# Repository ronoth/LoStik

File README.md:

# LoStik

LoStik is an affordable, easy to use, LoRaWAN™ compatible device. It lets IoT (Internet of Things) integrators, network testers, and hobbyists get connected to a LoRa® network faster, diagnose network issues more easily, and build new and exciting connected devices.  LoStik is currently available to purchase on [Crowd Supply](https://www.crowdsupply.com/third-venture/lostik) and [Connected Things Store](https://connectedthings.store/gb/search?controller=search&s=lostik).

## Examples

Python examples require Python 3.  Be sure to install the dependiencies in requirements.txt

    pip install -r requirements.txt

### Miniterm

miniterm.py is a light weight terminal emulator that works well with LoRa stick. 
The RN2903/R2483 radios require \r\n line ending and run at 57600 baud.

    ./miniterm.py --echo /dev/ttyUSB0 57600

### Blinky

blinky.py is for testing the user LEDs on the LoRa Stik.  There is a red led tied to GPIO11 and a blue led tied to GPIO10. 

    ./blinky.py  -m blue -d 1 /dev/ttyUSB0

will blink the blue led once per second

    ./blinky.py -m both -d .5 /dev/ttyUSB0

will alternate the blue and red leds every .5 seconds.

### Packet Radio

radio_receiver.py and radio_sender.py are used for sending LoRa packets between two LoRa Stiks without the need for a LoRaWAN gateway.  The included example sends a unix timestamp packet every 2 seconds and the receiver prints the incoming packets to stdout.

## Resources

For detailed infomation about available commands checkout one of the following docs:
* [RN2903 Command Reference](http://ww1.microchip.com/downloads/en/DeviceDoc/40001811A.pdf)
* [RN2843 Command Reference](http://ww1.microchip.com/downloads/en/DeviceDoc/40001784B.pdf)

### GUI
Microchip offers a programm called "Lora Dev Utility" that is part of the [LoRa Development Suite](https://www.microchip.com/developmenttools/ProductDetails/dv164140-1)

## Platform Notes

For platform specific notes see:

* [Windows](docs/windows.md)
* [Mac](docs/mac.md)
* [Linux](docs/linux.md)

## License

### Software

All software and example scripts are MIT licensed.  For details see [LICENSE](blob/master/LICENSE)

### Hardware
Hardware design and schematics are licenede under Creative Commons CC-BY-SA-NC  For details see [hardware/LICENSE.md](blob/master/hardware/LICENSE.md)

### User LEDS

LoStik has two user LEDs that you can control via the UART interface on GPIO10 and GPIO11 and can be accessed using the following commands:

```sys set pindig GPIO10 1``` (turns on blue LED)

```sys set pindig GPIO10 0``` (turns off blue LED)

```sys set pindig GPIO11 1``` (turns on red LED)

```sys set pindig GPIO11 0``` (turns off red LED)

<sup>LoRa® and LoRaWAN™ are trademarks of Semtech Corporation or its subsidiaries.</sup>

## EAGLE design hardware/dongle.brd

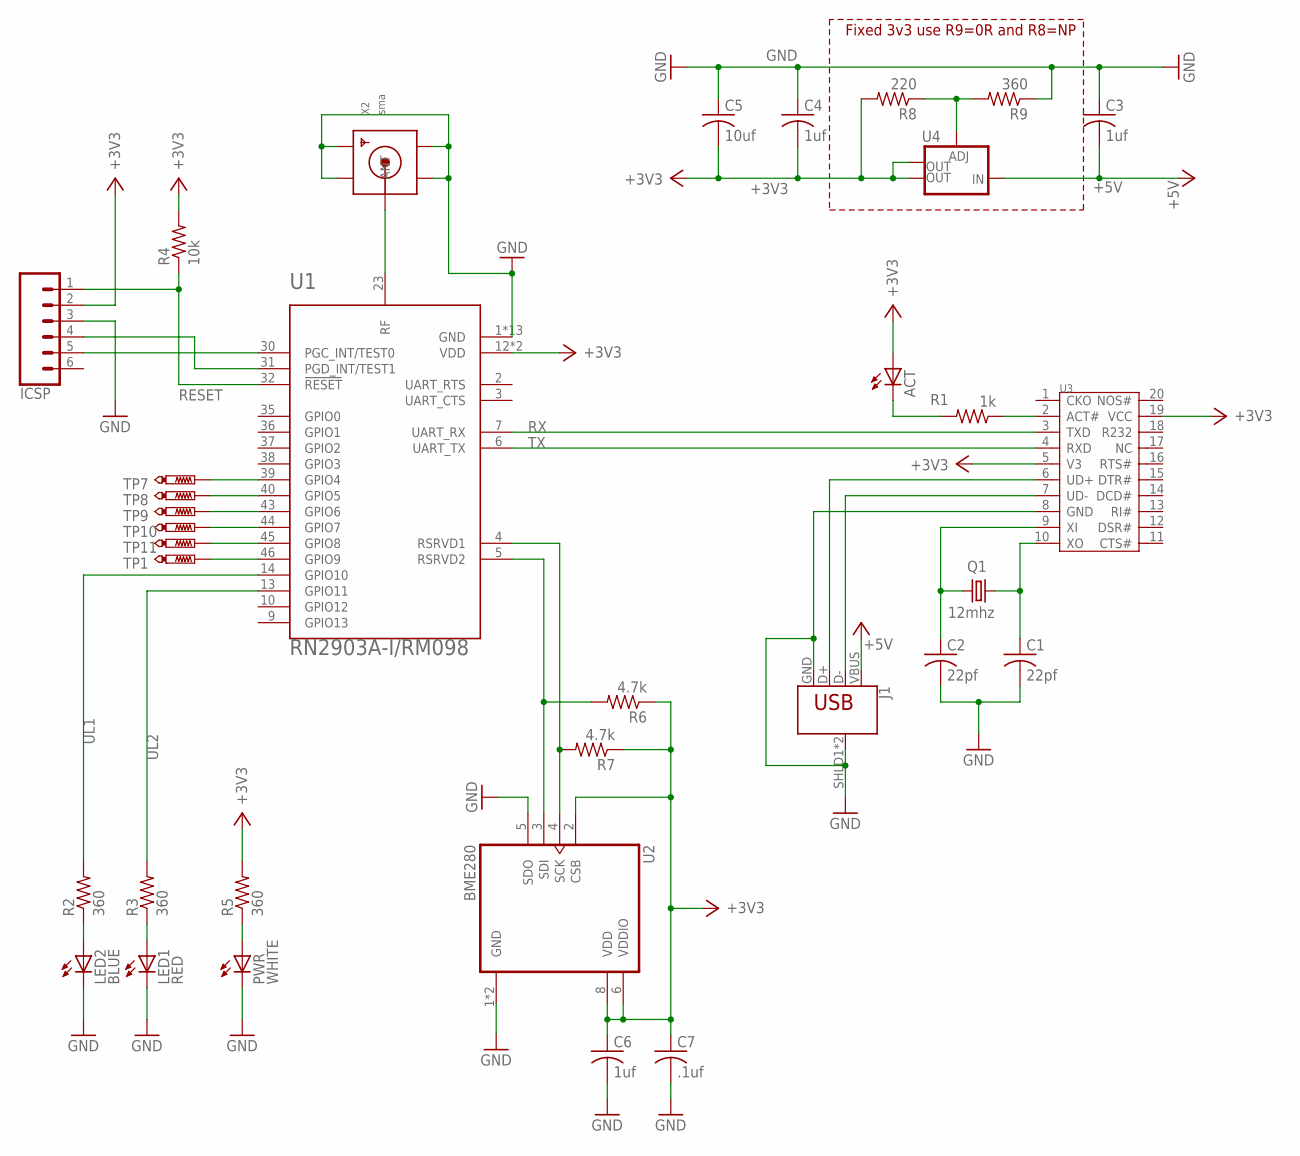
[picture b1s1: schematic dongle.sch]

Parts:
ACT: LEDCHIP-LED0603; CHIP-LED0603
C1, C2: 22pf; C0603K
C3, C4, C6: 1uf; C0603K
C5: 10uf; C1206K
C7: .1uf; C0603K
ICSP: CONN_06SMD-FEMALE-V2; 1X06-SMD-FEMALE
J1: USB_A_PTH_MALE; USB-A-H
LED1: RED; CHIP-LED0603
LED2: BLUE; CHIP-LED0603
PWR: WHITE; CHIP-LED0603
Q1: 12mhz; SM49
R1: 1k; R0603
R2, R3, R5, R9: 360; R0603
R4: 10k; R0603
R6, R7: 4.7k; R0603
R8: 220; R0603
TP1, TP7, TP8, TP9, TP10, TP11: PTR1B1,27; B1,27
U1: RN2903A-I/RM098; XCVR_RN2903A-I/RM098
U2: BME280; PSON65P250X250X100-8N
U3: INTERFACE-CH340T(SSOP20); SSOP20-0.65-7.6X5.2MM
U4: V_REG_LM1117SOT223; SOT223
X2: sma; SMA_EDGELAUNCH

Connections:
+3V3: ACT.A, C4.2, C5.2, C6.1, C7.1, ICSP.2, R4.2, R5.2, R6.1, R7.1, R8.2, U1.12 (VDD), U1.34 (VDD), U2.2 (CSB), U2.6 (VDDIO), U2.8 (VDD), U3.5 (V3), U3.19 (VCC), U4.2 (OUT), U4.4 (OUT)
+5V: C3.2, J1.VBUS, U4.3 (IN)
GND: C1.2, C2.2, C3.1, C4.1, C5.1, C6.2, C7.2, ICSP.3, J1.GND, J1.SHLD1 (SHIELD), J1.SHLD2 (SHIELD), LED1.C, LED2.C, PWR.C, R9.1, U1.1 (GND), U1.8 (GND), U1.11 (GND), U1.20 (GND), U1.21 (GND), U1.22 (GND), U1.24 (GND), U1.26 (GND), U1.27 (GND), U1.28 (GND), U1.33 (GND), U1.41 (GND), U1.47 (GND), U2.1 (GND), U2.5 (SDO), U2.7 (GND), U3.8 (GND), X2.GND@1 (GND4), X2.GND@2 (GND3), X2.GND@3 (GND2), X2.GND@4 (GND1)
unnamed: U1.23 (RF), X2.P (ANT)
unnamed: R1.1, U3.2 (ACT#)
unnamed: ACT.C, R1.2
unnamed: J1.D+, U3.6 (UD+)
unnamed: J1.D-, U3.7 (UD-)
unnamed: C1.1, Q1.1, U3.10 (XO)
unnamed: C2.1, Q1.2, U3.9 (XI)
unnamed: ICSP.4, U1.31 (PGD_INT/TEST1)
unnamed: ICSP.5, U1.30 (PGC_INT/TEST0)
unnamed: R7.2, U1.4 (RSRVD1), U2.4 (SCK)
unnamed: R6.2, U1.5 (RSRVD2), U2.3 (SDI)
unnamed: LED2.A, R2.1
unnamed: LED1.A, R3.1
unnamed: PWR.A, R5.1
unnamed: TP1.TP, U1.46 (GPIO9)
unnamed: R8.1, R9.2, U4.1 (ADJ)
unnamed: TP7.TP, U1.39 (GPIO4)
unnamed: TP8.TP, U1.40 (GPIO5)
unnamed: TP9.TP, U1.43 (GPIO6)
unnamed: TP10.TP, U1.44 (GPIO7)
unnamed: TP11.TP, U1.45 (GPIO8)
RESET: ICSP.1, R4.1, U1.32 (!RESET)
RX: U1.7 (UART_RX), U3.3 (TXD)
TX: U1.6 (UART_TX), U3.4 (RXD)
UL1: R2.2, U1.14 (GPIO10)
UL2: R3.2, U1.13 (GPIO11)

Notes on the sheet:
Fixed 3v3 use R9=0R and R8=NP

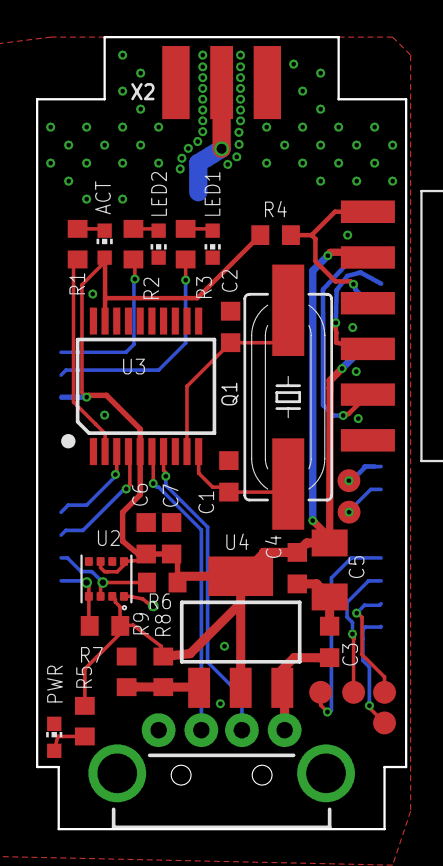
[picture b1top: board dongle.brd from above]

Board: 2 copper layers, 20.5 x 44.0 mm, 35 parts (1 on the bottom side), 29 nets.

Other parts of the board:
U$1: 1551USB2

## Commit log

2018-06-16 hardware files
2018-06-16 examples
2018-06-23 packed mode reciever
2018-06-23 move reciever file
2018-06-23 packet radio sender
2018-06-25 code cleanup and readme
2018-07-02 license info
2018-07-02 Fix "non scriptable" issue
2018-07-14 more readme
2018-11-21 Add example for The Things Network
2018-12-09 Add info about user leds
    Adding information about user leds in readme per @WA4OSH
2018-12-10 improve sender to show frame count, blink properly
2018-12-10 lorawan example
2019-02-25 Rewrite radio_sender example to use serial.threaded.LineReader
2019-03-07 Improved documentation
2019-03-07 update readme with gui link and platofrm notes
2019-03-07 linux docs
2019-03-07 windows update
2019-03-14 Created Swift package
2019-03-14 Added System commands
2019-03-14 Updated unit tests
2019-03-14 Working on commands
2019-03-14 Fixed serial read / write
2019-03-14 Working on System commands
2019-03-14 API Improvements
2019-03-14 Completed system commands
2019-03-14 Working on Mac commands
2019-03-15 Working on Radio commands
2019-03-15 Removed duplicate sources
2019-03-15 Fixed parsing Hexadecimal string
2019-04-22 channel configuration
2019-04-30 hannel configuration'
2019-04-30 minor config documentation
2019-05-02 Fixes for lorawan example
2019-05-02 improvements to configure script
2019-05-03 fix use of status instead of state
2019-09-02 production tester for linux
2023-01-17 Add purchase link to Readme
    Added link to https://connectedthings.store/

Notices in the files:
parts and their libraries:
SparkFun-Connectors: Licensing: Creative Commons ShareAlike 4.0 International - https://creativecommons.org/licenses/by-sa/4.0
